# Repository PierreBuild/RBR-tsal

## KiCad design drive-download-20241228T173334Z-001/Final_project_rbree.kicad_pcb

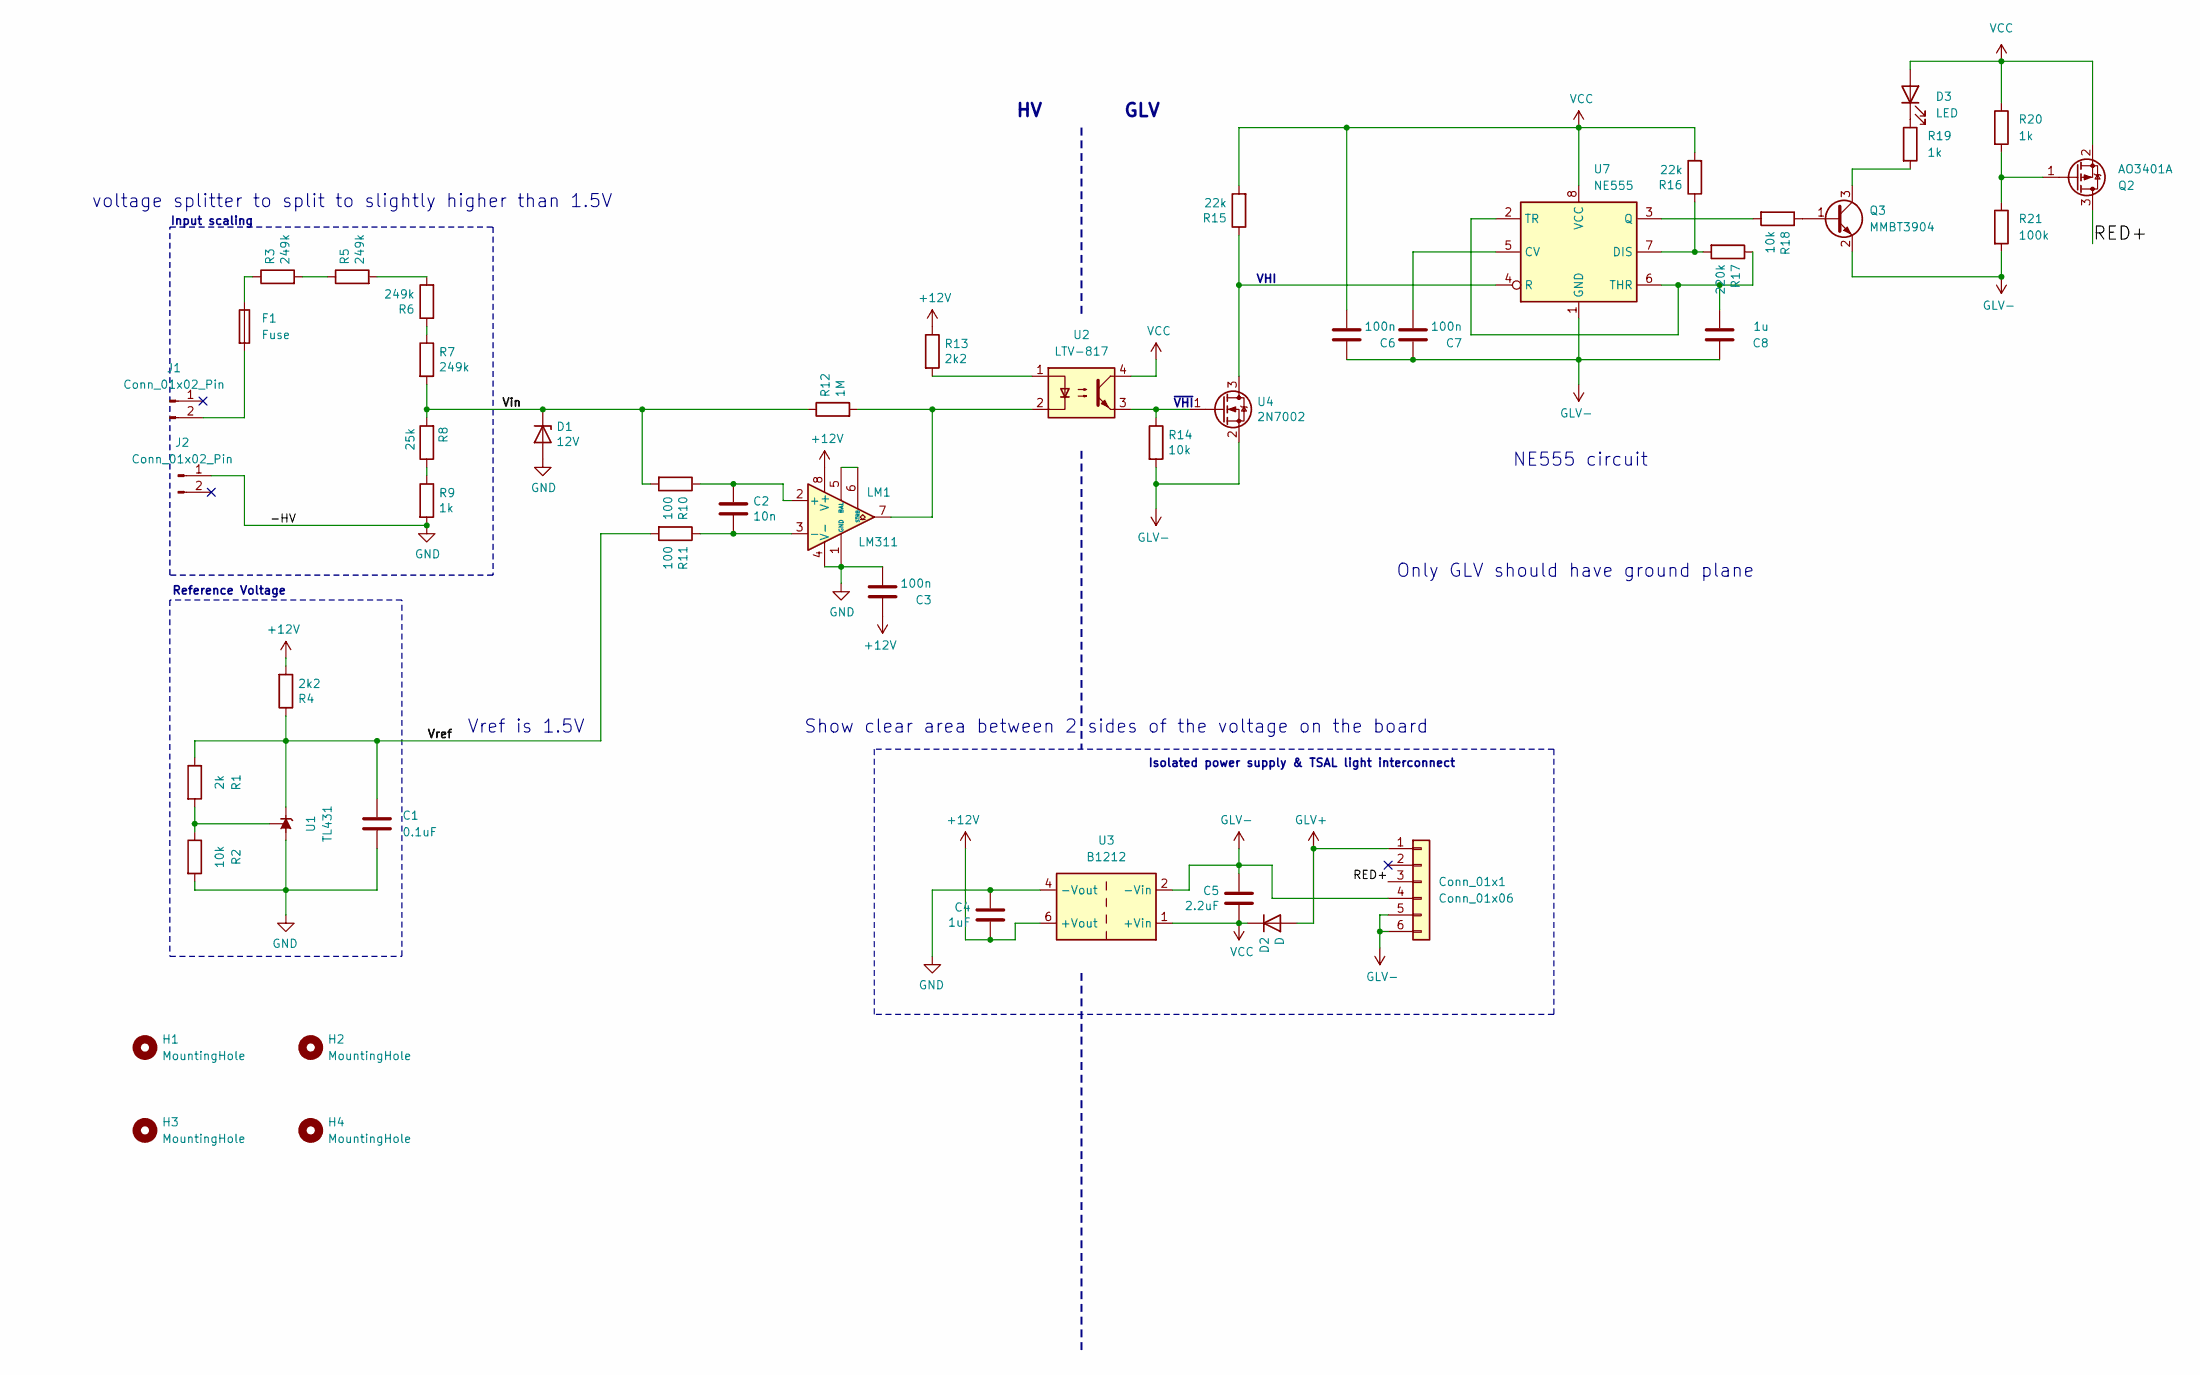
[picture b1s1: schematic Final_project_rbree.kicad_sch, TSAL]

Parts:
C1: 0.1uF; C_0805_2012Metric_Pad1.18x1.45mm_HandSolder
C2: 10n; C_0805_2012Metric_Pad1.18x1.45mm_HandSolder
C3, C6, C7: 100n; C_0805_2012Metric_Pad1.18x1.45mm_HandSolder
C4: 1uF; C_0805_2012Metric_Pad1.18x1.45mm_HandSolder
C5: 2.2uF; C_0805_2012Metric_Pad1.18x1.45mm_HandSolder
C8: 1u; C_0805_2012Metric_Pad1.18x1.45mm_HandSolder
Conn_01x1: Conn_01x06; JST_VH_B6P-VH_1x06_P3.96mm_Vertical
D1: 12V; D_DO-35_SOD27_P7.62mm_Horizontal
D2: D; D_0805_2012Metric_Pad1.15x1.40mm_HandSolder
D3: LED; LED_0805_2012Metric_Pad1.15x1.40mm_HandSolder
F1: Fuse; Fuse_0805_2012Metric_Pad1.15x1.40mm_HandSolder
H1, H2, H3, H4: MountingHole; MountingHole_3mm
J1, J2: Conn_01x02_Pin; AMASS_XT60-M_1x02_P7.20mm_Vertical
LM1: LM311; SOIC-8_3.9x4.9mm_P1.27mm
Q2: AO3401A; SOT-23_Handsoldering
Q3: MMBT3904; SOT-23_Handsoldering
R1: 2k; R_0805_2012Metric
R2, R14, R18: 10k; R_0805_2012Metric
R3, R5, R6, R7: 249k; R_0805_2012Metric
R4, R13: 2k2; R_0805_2012Metric
R8: 25k; R_0805_2012Metric
R9, R19, R20: 1k; R_0805_2012Metric
R10, R11: 100; R_0805_2012Metric
R12: 1M; R_0805_2012Metric
R15, R16: 22k; R_0805_2012Metric
R17: 220k; R_0805_2012Metric
R21: 100k; R_0805_2012Metric
U1: TL431; SOT-23_Handsoldering
U2: LTV-817; SOP-4_4.4x2.6mm_P1.27mm
U3: B1212; Converter_DCDC_TRACO_TBA2-xxxx_Single_THT
U4: 2N7002; SOT-23_Handsoldering
U7: NE555; SOIC-8_3.9x4.9mm_P1.27mm

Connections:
+12V: C3.1, C4.2, LM1.8 (V+), R4.2, R13.1, U3.6 (+Vout)
/RED+: Conn_01x1.3, Q2.3 (D)
/Vin: D1.1 (K), R7.2, R8.2, R10.2, R12.1
/Vref: C1.1, R1.1, R4.1, R11.2, U1.3 (K)
GLV+: Conn_01x1.1, D2.2 (A)
GLV-: C5.1, C6.1, C7.1, C8.1, Conn_01x1.4, Conn_01x1.5, Conn_01x1.6, Q3.2 (E), R14.2, R21.2, U3.2 (-Vin), U4.2 (S), U7.1 (GND)
GND: C1.2, C3.2, C4.1, D1.2 (A), J2.1, LM1.1 (GND), LM1.4 (V-), R2.2, R9.2, U1.2 (A), U3.4 (-Vout)
unnamed: D3.1 (K), R19.1
unnamed: F1.1, R3.1
unnamed: F1.2, J1.2
unnamed: C2.1, LM1.2 (+), R10.1
unnamed: C2.2, LM1.3 (-), R11.1
unnamed: LM1.5 (BAL), LM1.6 (STRB)
unnamed: LM1.7, R12.2, U2.2
unnamed: Q2.1 (G), R20.2, R21.1
unnamed: Q3.1 (B), R18.1
unnamed: Q3.3 (C), R19.2
unnamed: R3.2, R5.1
unnamed: R5.2, R6.2
unnamed: R6.1, R7.1
unnamed: R8.1, R9.1
unnamed: R13.2, U2.1
unnamed: R1.2, R2.1, U1.1 (REF)
unnamed: R15.1, U4.3 (D), U7.4 (R)
unnamed: R14.1, U2.3, U4.1 (G)
unnamed: C7.2, U7.5 (CV)
unnamed: R16.1, R17.2, U7.7 (DIS)
unnamed: R18.2, U7.3 (Q)
unnamed: C8.2, R17.1, U7.2 (TR), U7.6 (THR)
VCC: C5.2, C6.2, D2.1 (K), D3.2 (A), Q2.2 (S), R15.2, R16.2, R20.1, U2.4, U3.1 (+Vin), U7.8 (VCC)

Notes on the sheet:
voltage splitter to split to slightly higher than 1.5V
Show clear area between 2 sides of the voltage on the board
Isolated power supply & TSAL light interconnect
Reference Voltage
~{VHI}
Input scaling
Only GLV should have ground plane
GLV
VHI
Vref is 1.5V
NE555 circuit

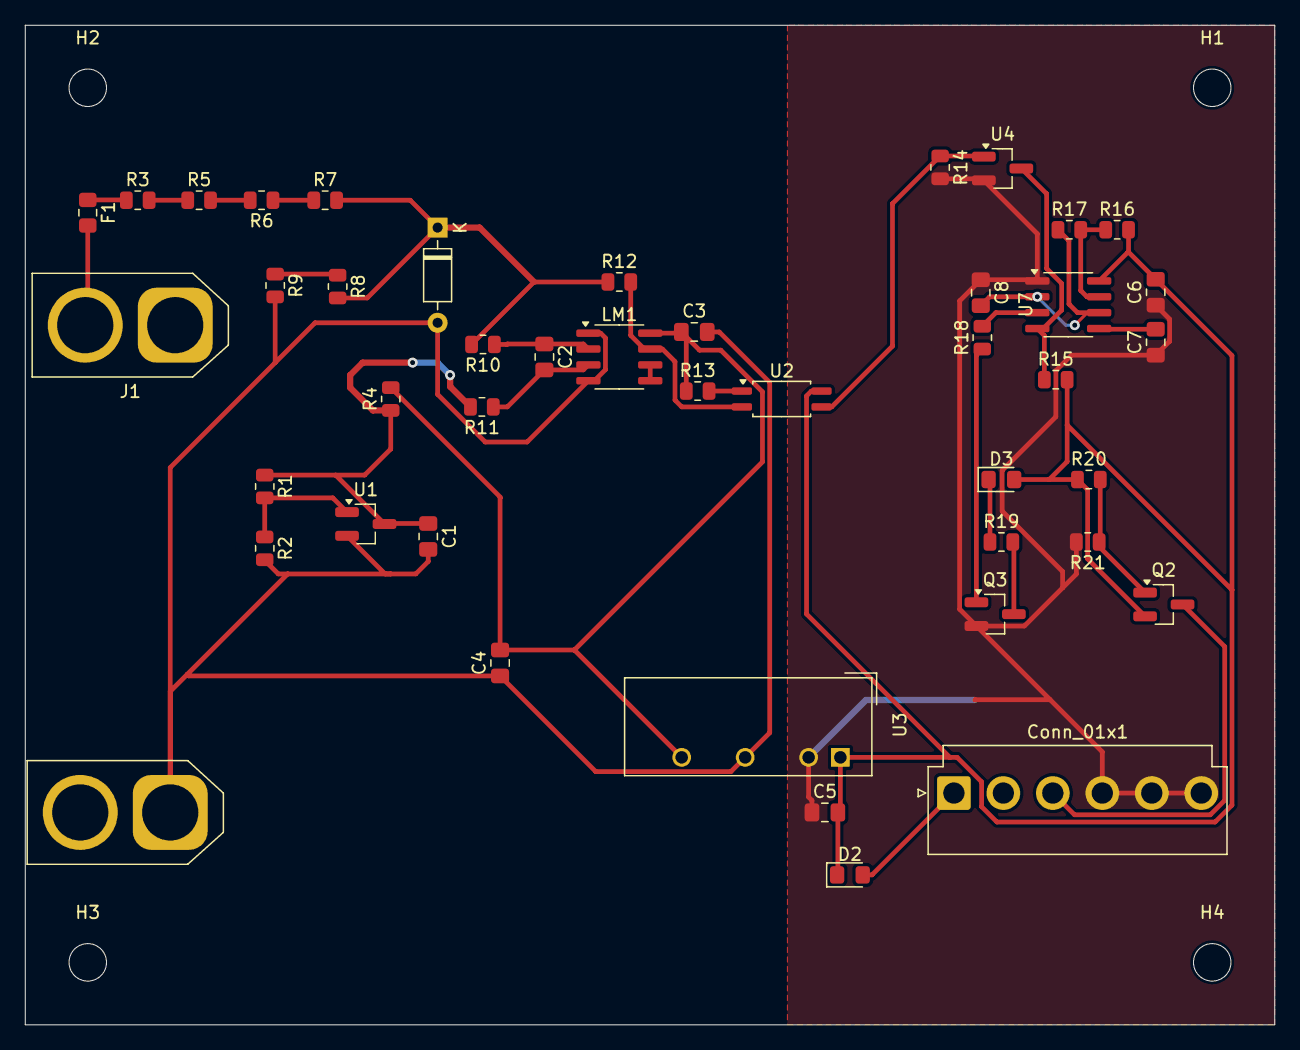
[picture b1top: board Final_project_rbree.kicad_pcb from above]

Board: 2 copper layers, 100.0 x 80.0 mm, 48 parts (0 on the bottom side), 30 nets.
